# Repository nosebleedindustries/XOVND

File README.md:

# XOVND · web

Source for **xound.com** — `https://xovnd.com`.

## Stack

- **Next.js 14** (App Router, JSX — TypeScript migration deferred)
- **React 18**
- Static CSS in `app/globals.css` (merged from the original
  shared / auth / walkthrough stylesheets + per-page inline `<style>`
  blocks; Tailwind migration deferred)
- Vercel hosting, auto-deploy on push to `main`
- All sales currently route to **Moonbase hosted checkout** at
  `https://xound.moonbase.sh/buy/clvster`

## Status

**Phase 2B.1 — Next.js migration in progress.**

The Babel-in-browser multi-page static site has been ported to a
Next.js 14 App Router project. Two critical pages (landing `/` and
CLVSTER product `/clvster`) are fully ported. The remaining pages
(`/account`, `/subscription`, `/trials`, `/support`, `/forum`,
`/admin`, `/auth`, `/walkthrough`) are placeholder stubs that share
the header/footer chrome and link back to the legacy reference.

Original JSX files preserved under [`legacy/`](./legacy/) for
incremental porting.

## Routes

| Route | File | Status |
|---|---|---|
| `/` | `app/page.jsx` | ✅ ported |
| `/clvster` | `app/clvster/page.jsx` | ✅ ported (BUY → Moonbase) |
| `/trials` | `app/trials/page.jsx` | ✅ ported |
| `/account` | `app/account/page.jsx` | 🚧 placeholder |
| `/subscription` | `app/subscription/page.jsx` | 🚧 placeholder |
| `/support` | `app/support/page.jsx` | 🚧 placeholder |
| `/forum` | `app/forum/page.jsx` | 🚧 placeholder |
| `/admin` | `app/admin/page.jsx` | 🚧 placeholder |
| `/auth` | `app/auth/page.jsx` | 🚧 placeholder |
| `/walkthrough` | `app/walkthrough/page.jsx` | 🚧 placeholder |

## Local dev

```bash
npm install
npm run dev          # http://localhost:3000
```

`npm run build` for production build; `npm start` to serve it locally.

## Deploy

Vercel auto-detects Next.js, no config needed. Push to `main` →
auto-deploy to production. Push to any other branch → preview deploy
URL appears in PR / commit.

## Roadmap

Phase 2B detailed checklist in
[`docs/roadmap/Phase2B-Backend.md`](./docs/roadmap/Phase2B-Backend.md):
Supabase auth + DB, Moonbase webhook handler, support tickets, forum
threads, admin analytics, promotion management, email infrastructure,
SEO, mailing list, analytics.

## Shared infrastructure

- **Domain**: Cloudflare Registrar (`xovnd.com`)
- **DNS**: Cloudflare (with Vercel CNAMEs as `DNS only` — don't proxy)
- **Email**: Cloudflare Email Routing — `joan@xovnd.com` → Gmail
- **Hosting**: Vercel (free hobby tier)
- **Future**: Supabase (Postgres + Auth), Resend (email), Plausible
  (analytics), Sentry (errors), EmailOctopus (mailing list)

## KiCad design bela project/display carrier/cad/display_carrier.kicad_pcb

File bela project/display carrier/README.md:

# Display carrier — 2× LILYGO T-Display-S3 Long

A carrier PCB that mounts **two T-Display-S3 Long** AMOLED bars (ESP32-S3, 640×180)
**landscape and butted** as one wide ~1280×180 UI strip, and **sandwiches onto the
Beagle+Bela** via the PocketBeagle-2 header block (`U1`).

**This is the TOP board of the stack**, so **all connectors sit on the BACK (`B.Cu`)** —
`U1` (PB2 sandwich header), `JA`, `JB` and `J_PWR` face **down** into the Beagle+Bela
sandwich, while the two displays stay on the **front (`F.Cu`), facing up**. See
`renders/ensemble_stack_side.png` / `ensemble_stack_front.png` for the assembled stack.

**`U1` is at the carrier's RIGHT edge** (KiCad x≈165, below DS2): the Beagle+Bela sandwich
sits at that edge so the **Bela's audio jacks clear the carrier and reach a free panel edge**
(they'd be buried mid-board with U1 centred). Trade-off: the two displays sit to the left of
the sandwich (asymmetric). `JB` moved to x≈110 to clear the shifted U1.

**`U1` = MALE 2×18 pin headers** (`PinHeader_2x18_P2.54mm_Vertical` ×2), pins pointing
**down** so the carrier plugs into female sockets on top of the sandwich — you can't
mate two female sockets. `JA`/`JB` are **FEMALE 2×15 P1.27 mm sockets on the FRONT (`F.Cu`, display side)**
that **mirror the LILYGO module's own `P5` 30-pin breakout** — each display plugs straight down into its
socket for **power + data** (`+5V` on P5 pin 27 · `GND` · `TX` · `RX`), no cable. Each socket's pad-centre is
placed **coincident with the module's factory `P5` connector**, verified in the exported STEP (socket centre =
`P5` body centre to ±0.1 mm): DS1 `P5` at (69.9, 31.3), DS2 `P5` at (128.9, 18.7) — so the male `P5` inserts
into the socket receptacle and the panel seats at its true height. (The two sockets sit at opposite ends of
their panels because the modules are mirror-mounted — `P5` is off-centre on the module.)
The `ensemble_*` renders show the full stack aligned + sandwiched: `U1` sits over the
Beagle's P1/P2 headers and its pins insert into the sandwich; the MIDI board is the
ribbon satellite in front.

- The panels are **smart satellites** — each ESP32 renders its own graphics, so the
  carrier only carries **power + a PRU-serial link** to each (Bela Gem leaves no HW
  UART/SPI free — see `../docs/display-architecture.md`). PRU0→panel A, PRU1→panel B.
- `JA` / `JB` (2×15 P1.27 mm, = LILYGO `P5`): the panel plugs straight in — `+5V`(P5 pin 27) `· GND · TX · RX`.
- Displays are **mounted mirror-symmetric** (USB-C/electronics outward, screens meeting
  in the middle) for a continuous face. Module = **27.2 × 88.8 × 11.1 mm** (factory STEP).

Board ≈ **194 × 81 mm**, 2-layer, AISLER rules, with a 7 mm mounting border carrying
**4× M2.5 corner holes** (`H1–H4`). The wide board is carried on **4 brass M2.5 hex
standoffs (~23 mm)** from the enclosure floor to the corners — the central U1 header does
the wiring, the corner legs do the holding. `scripts/add_mounts.py` grows the border +
holes on the routed board (routing untouched; the new margin is a bare mounting border).

## Assembled stack height (male pins fully seated)
Measured from the factory 3D models with the carrier's 2×18 male header pushed **fully** into
the sandwich's female connector: **total PCB-stack height ≈ 36.2 mm** (device base → display glass).
- PocketBeagle 2 (PCB + headers): 0 → 8.7 mm
- Bela Gem (mated cape, PCB 11.7–13.3): **audio jacks up to 21.8 mm ← the limiting component**
- Carrier PCB: 22.8 → 24.4 mm (1 mm above the Bela jacks; male pins ~6 mm into the female)
- T-Display module → glass top: **36.19 mm**

**The height floor is the Bela's LINE IN/OUT jacks (21.8 mm)** — the carrier can't sit lower
without hitting them, so the male pins can only insert as far as that clearance allows. Lower-profile
or relocated jacks would let the stack compress further. Add the 1 mm aluminium enclosure +
top/bottom clearances (~3–5 mm) for the external height (~40–41 mm).

## Notes / to refine
- The `TDisplayS3Long` footprint's **mounting-hole positions are estimates** + the active-
  area seam offset should be verified against the factory DWG (`dimensions/` in the LILYGO
  repo) or a physical unit — then nudge the two modules for a perfect join.
- 3D model = the factory **`H685-PCB-3D.stp`** (from `T-Display-S3-Long-PCB-3D.zip`, LILYGO
  GitHub `dimensions/`) — not committed (7.75 MB); the footprint references it by path.

## Routing (done)
**Fully routed + fab-ready.** Freerouting 2.2.4, 2-layer (both signal). A parallel **clearance
sweep** {0.15, 0.175, 0.20, 0.25 mm} picked **0.25 mm** as the loosest that still routes clean
(most fab margin), then **GND poured on F.Cu + B.Cu** (solid pad connection), netclass clearance
**0.15 mm** (AISLER). Result: **0 unconnected, 68 tracks, 1 via, 0 hard DRC** (only 2 cosmetic
silk warnings — DS ref field near the edge + DS1/DS2 silk-rect overlap). Authoritative check =
`kicad-cli pcb drc` (verified: 0 shorting, 0 clearance, GND filled both layers, connectors on B.Cu).
Scripts: `scripts/carrier_export_dsn.py` (DSN, strips fp graphics by text so KiCad's exporter
doesn't choke on the big display outlines) + `scripts/carrier_route_variant.py <µm>` (one full
clearance variant → JSON). Routed back-side view: `renders/carrier_routed_bottom.png`.

## Power (rev: dedicated input)
The two AMOLEDs are hungry (~0.4–1 A peak), so they are **NOT** powered from the Beagle rail.
- **`J_PWR`** (2-pin screw terminal) = **+5V / GND** straight from the main PSU → feeds `JA`/`JB` → the panels.
- The **PB2 sandwich header (`U1`) carries only GND (common reference) + the data lines** (TX/RX/RST per panel).
- So display current never flows through the Beagle→Gem→carrier stack — the audio rail stays clean.

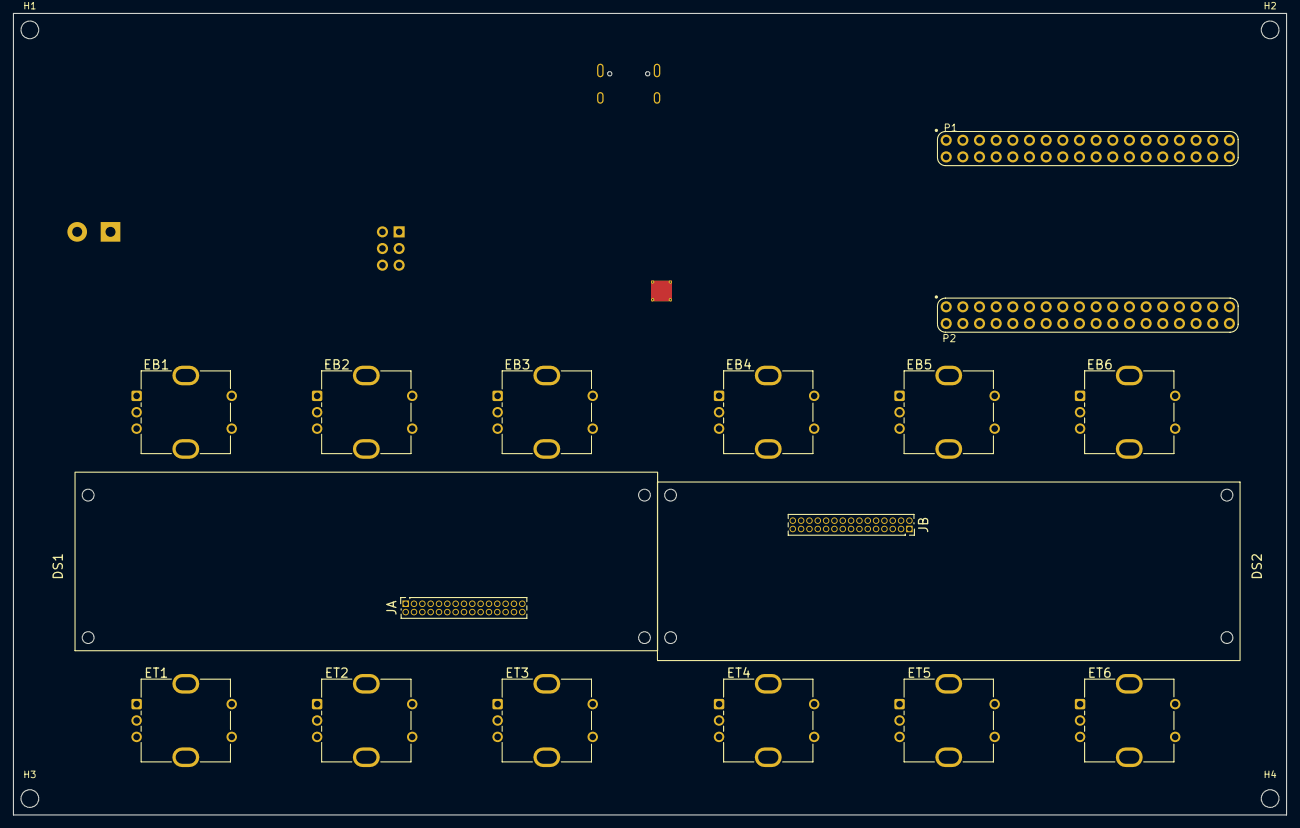
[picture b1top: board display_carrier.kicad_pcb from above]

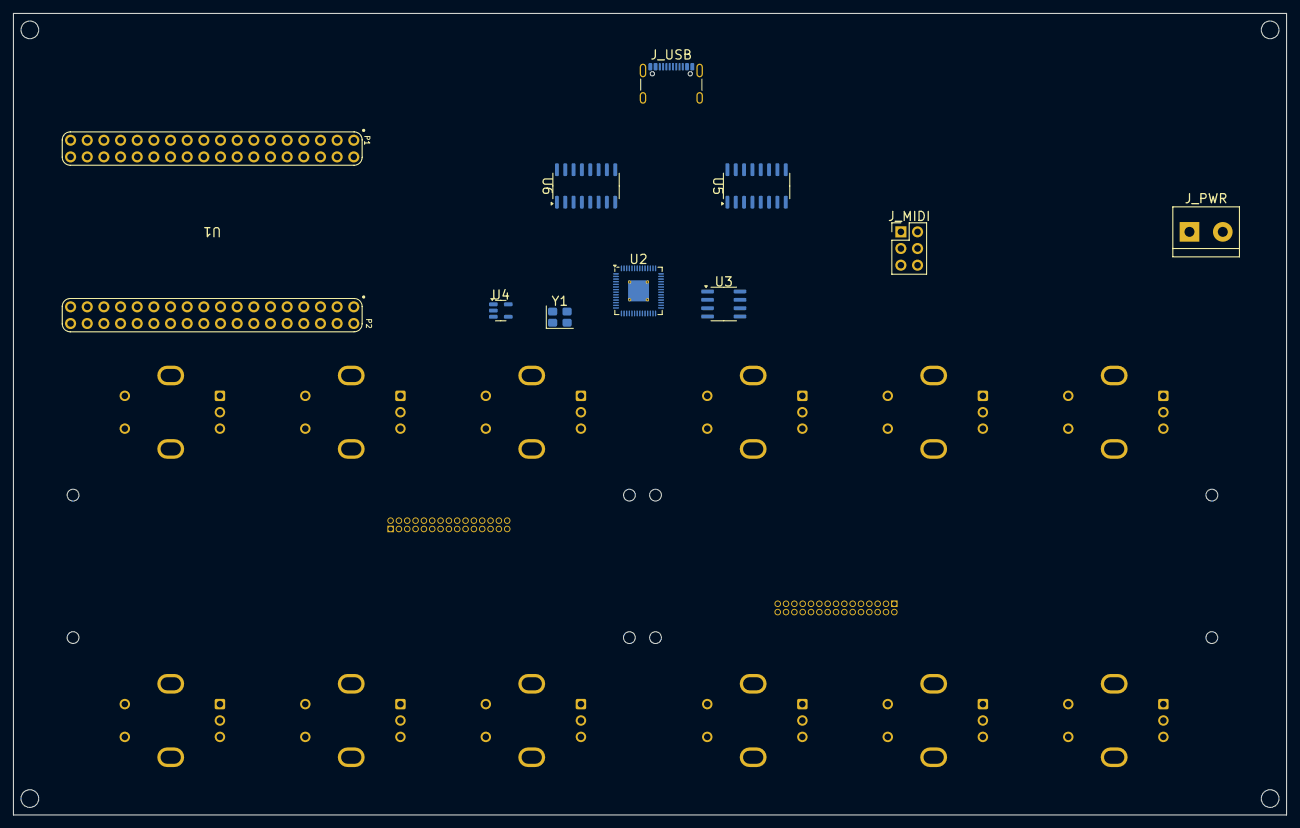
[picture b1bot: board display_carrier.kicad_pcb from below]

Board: 2 copper layers, 194.1 x 122.2 mm, 30 parts (10 on the bottom side), 9 nets, no tracks yet.

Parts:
DS1, DS2: T-Display-S3-Long; TDisplayS3Long
EB1, EB2, EB3, EB4, EB5, EB6: ENC; RotaryEncoder_PEC12R_Vertical
ET1, ET2, ET3, ET4, ET5, ET6: ENC; RotaryEncoder_PEC12R_Vertical
H1, H2, H3, H4: MountingHole_2.7mm_M2.5
JA: DISP_A; PinSocket_2x15_P1.27mm_Vertical
JB: DISP_B; PinSocket_2x15_P1.27mm_Vertical
J_MIDI: MIDI_HUB; PinHeader_2x03_P2.54mm_Vertical
J_PWR: PWR_IN; TerminalBlock_bornier-2_P5.08mm
J_USB: USB; USBC
U1: PocketBeagle2; PB2
U2: RP2040; RP2040_QFN56
U3: W25Q128; Flash_SOIC8
U4: 3V3; LDO_SOT235
U5, U6: 74HC165; SR_74HC165_SOIC16
Y1: 12MHz; XTAL_3225

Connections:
+3V3: J_MIDI.1, U1.P2.23 (3.3V)
+5V: JA.27, JB.27, J_PWR.1
DA_RX: JA.16, U1.P1.31 (PRU0.4)
DA_TX: JA.18, U1.P1.29 (PRU0.7)
DB_RX: JB.16, U1.P2.30 (PRU1.12)
DB_TX: JB.18, U1.P2.28 (PRU1.15)
GND: JA.1, JA.2, JB.1, JB.2, J_MIDI.2, J_MIDI.5, J_PWR.2, U1.P1.16 (GND), U1.P2.15 (GND)
MIDI_RX: J_MIDI.3, U1.P2.32 (PRU1.11)
MIDI_TX: J_MIDI.4, U1.P2.34 (PRU1.14)

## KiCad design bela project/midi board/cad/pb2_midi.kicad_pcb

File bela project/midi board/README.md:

# PocketBeagle 2 — MIDI board (TRS MIDI IN/OUT)

A small script-generated carrier PCB that adds **MIDI IN + MIDI OUT** (3.5 mm TRS
Type-A) to a **PocketBeagle 2**, designed to sit alongside the
[Bela Gem](https://bela.io/products/bela-gem-stereo-and-multi/) audio sandwich and
connect by a **6-way ribbon cable** — so the whole device stays thin.

Companion to the [Bela Gem CAD model](../README.md).

## What it is
- **MIDI IN** — opto-isolated (H11L1M) TRS-A input.
- **MIDI OUT** — resistor-driven TRS-A output.
- **Ribbon-connected** to the Beagle via `J3` (2×3 right-angle header), taps 4 pins of
  header **P2**: `+3V3 = P2.23`, `GND = P2.15`, `UART_RX = P2.5`, `UART_TX = P2.7`
  (**UART4** — chosen to avoid the Linux console UART0 and the Bela audio pins).
- **Jacks matched to the Bela audio jacks**: same **Lumberg 1503-03** part, same
  **10.7 mm** spacing, and mounted on **4× M2.5 hex standoffs** so the MIDI jacks land at
  the same panel plane and height (Z ≈ 16.2 mm) as the audio jacks — everything aligns on
  one enclosure face behind a **1 mm folded/laser-cut cover**.
- **Power on/off button** (`SW1`, Alps SKRTLAE010 side-actuated SMD): sits **in the same
  panel row, 10.7 mm** from the last jack, actuator co-planar with the jack fronts (X = 60.6).
  Soft-power to the Beagle via `J4` (`PWR_BTN`/`GND`/`+3V3`), conditioned on-board with
  `R5` (10 k pull-up, active-low) + `C3` (100 n debounce).
  - ⚠ **Set SW1's rotation so the actuator faces the panel edge** (verify vs the SKRTLAE010
    datasheet — no 3D model ships in KiCad, it's modelled by hand in the assembly). The
    actuator is a couple mm lower than the jack axis on a bare board; a tall side-switch or a
    ~1.7 mm riser puts it exactly on the jack centreline if you want the holes perfectly level.

Board: **44 × 40 mm**, single-sided population, 2-layer (AISLER rules).

## Files
```
cad/
  pb2_midi.kicad_pcb                 the board (KiCad 9)
  pb2_midi.step                      board 3D (STEP)
  pb2_midi_aligned_assembly.step     full aligned device: Bela sandwich + this board on
                                     hex spacers + ribbon + shared 1mm panel with 4 holes
scripts/
  gen_pcb.py                         script that builds the .kicad_pcb (parts + nets + DRC)
  merge_aligned.py                   builds the aligned assembly STEP (jack matching + spacers)
  merge_hat.py                       earlier viz (Gem hat + slim board + ribbon)
lib.pretty/                          footprints used (PB2, Lumberg jack, opto, header, holes)
renders/                             board render + connection-header diagram
bom.csv
```

## MIDI wiring
TRS **Type-A**: Tip = DIN-5, Ring = DIN-4, Sleeve = DIN-2.
- **IN:** J1.R → R1(220) → opto LED anode; opto LED cathode ← J1.T; D1 across the LED.
  Opto output: R4(470) pull-up to +3V3, collector → `UART_RX`.
- **OUT:** `UART_TX` → R2(220) → J2.T (tip); +3V3 → R3(220) → J2.R (ring); J2.S → GND.

## ⚠ Electrical note — Gem + MIDI
`UART4` (P2.5/P2.7) is free **only when the Bela Gem is NOT fitted** (the Gem uses those
pins for audio). For a **standalone MIDI** PocketBeagle this ribbon board is correct. If
you want **Gem audio *and* MIDI on one Beagle**, run MIDI over **USB** instead — no free
serial UART is available with the Gem on.

## Rebuild
```
"C:/Program Files/KiCad/9.0/bin/python.exe" scripts/gen_pcb.py      # -> pb2_midi.kicad_pcb + DRC
kicad-cli pcb export step --subst-models --no-dnp -o cad/pb2_midi.step cad/pb2_midi.kicad_pcb
FreeCADCmd scripts/merge_aligned.py                                 # -> aligned assembly STEP
```

## Routing
Routed with **Freerouting 2.2.4** (2-layer, both F/B signal) then **GND poured on F.Cu + B.Cu**
(solid pad connection). AISLER 2-layer rules: track 0.25, space 0.15, via 0.7/0.3, edge 0.3.
- `scripts/route_export_dsn.py` → `routing/pb2_midi.dsn` (clearance 0.15) → Freerouting `-mp 40`
  → `routing/pb2_midi.ses` → `scripts/route_import_ses.py` (import + GND pour).
- **Result: routing_complete = True, 0 unconnected, 2 vias, GND plane both layers.**

```
kicad python  gen_pcb.py            # clean board
kicad python  route_export_dsn.py   # -> routing/pb2_midi.dsn
java -jar freerouting-2.2.4.jar -de routing/pb2_midi.dsn -do routing/pb2_midi.ses -mp 40
kicad python  route_import_ses.py   # import SES + pour GND -> pb2_midi.kicad_pcb
```

## Blender renders (process documentation)
Photoreal Cycles renders of the current build state live in `renders/blender_*.png`
(hero / detail / top). Pipeline via the **blender-mcp** socket:
- Boards exported from KiCad as **GLB with copper traces** (`kicad-cli pcb export glb
  --include-tracks --include-zones --include-silkscreen --include-soldermask`) — the MIDI
  board and the factory Bela Gem both show real traces + silk + soldermask.
- PocketBeagle 2 = STEP → OBJ. Case panel, hex spacers, ribbon, TRS jacks and the power
  button are built as Blender primitives (`blender/bl_build2.py`); 3-point + warm orange
  rim lighting, AgX view transform.
- `blender/bl.py` drives Blender over the addon socket (127.0.0.1:9876); `bl_import.py`
  imports + normalizes, `bl_build2.py` assembles + materials + Cycles, `bl_hero.py` renders.

## Status
- **Routed + GND-poured, fab-ready for AISLER.** Jacks + power button aligned to the Bela audio
  jacks (spacing/plane/height), hex-spacer mounts, DRC **0 errors / 0 unconnected**.
- Conservative KiCad courtyards were shrunk (jacks fit 10.7 mm as on the Bela) and footprint
  silkscreen graphics dropped. One residual **silk-over-copper warning** (C1 ref over its pad) —
  cosmetic; AISLER auto-clips silk off pads.

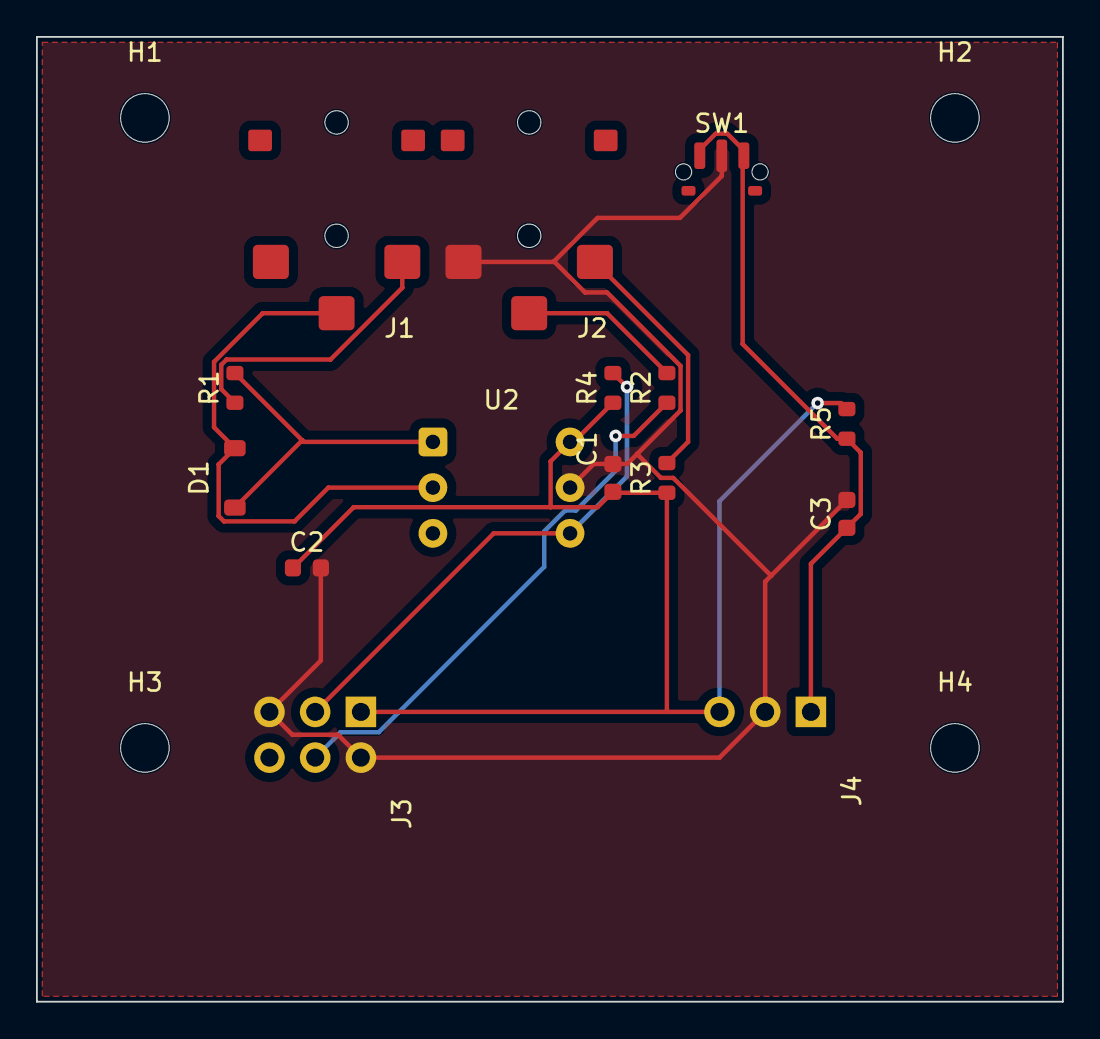
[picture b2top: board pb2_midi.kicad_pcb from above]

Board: 2 copper layers, 57.0 x 53.6 mm, 19 parts (0 on the bottom side), 10 nets.

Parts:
C1, C2, C3: 100n; C_0603_1608Metric
D1: 1N4148; D_SOD-123
H1, H2, H3, H4: M2.5; MountingHole_2.7mm_M2.5
J1: MIDI_IN; Jack_3.5mm_Lumberg_1503_03_Horizontal
J2: MIDI_OUT; Jack_3.5mm_Lumberg_1503_03_Horizontal
J3: RIBBON; PinHeader_2x03_P2.54mm_Horizontal
J4: PWR_HDR; PinHeader_1x03_P2.54mm_Horizontal
R1, R2, R3: 220; R_0603_1608Metric
R4: 470; R_0603_1608Metric
R5: 10k; R_0603_1608Metric
SW1: PWR; SW_Push_1P1T-MP_NO_Horizontal_Alps_SKRTLAE010
U2: H11L1M; DIP-6_W7.62mm

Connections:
+3V3: C1.1, C2.1, J3.1, J4.3, R3.1, R4.1, R5.2, U2.6
GND: C1.2, C2.2, C3.2, J2.S, J3.2, J3.5, J4.2, SW1.2, U2.5
MIDI_IN_A: D1.1, R1.2, U2.1
MIDI_IN_K: D1.2, J1.T, U2.2
MIDI_IN_RING: J1.R, R1.1
MIDI_OUT_RING: J2.R, R3.2
MIDI_OUT_TIP: J2.T, R2.2
PWR_BTN: C3.1, J4.1, R5.1, SW1.1
UART_RX: J3.3, R4.2, U2.4
UART_TX: J3.4, R2.1

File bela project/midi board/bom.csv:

Refs,Qty,Value,Footprint,MPN,Description
J1 J2,2,3.5mm TRS,Jack_3.5mm_Lumberg_1503_03_Horizontal,Lumberg 1503 03,MIDI IN / MIDI OUT — 3.5mm TRS Type-A jack (same part + 10.7mm spacing as the Bela audio jacks so they align on the panel)
SW1,1,PWR,SW_Push_1P1T-MP_NO_Horizontal_Alps_SKRTLAE010,Alps SKRTLAE010,Power on/off — side-actuated SMD momentary push button; soft-power to the Beagle. Placed in the panel row 10.7mm from J2 (actuator co-planar with the jack fronts). NOTE: set SW1 rotation so the actuator faces the panel edge (verify vs datasheet).
U2,1,H11L1M,DIP-6_W7.62mm,H11L1M,High-speed optocoupler — MIDI IN opto-isolation (1=Anode 2=Cathode 3=NC 4=Vo 5=GND 6=Vcc)
D1,1,1N4148,D_SOD-123,1N4148W-7-F,Reverse-protection diode across the opto input LED
R1,1,220,R_0603_1608Metric,RC0603FR-07220RL,MIDI IN current-limit resistor
R4,1,470,R_0603_1608Metric,RC0603FR-07470RL,Opto output pull-up to +3V3
R2 R3,2,220,R_0603_1608Metric,RC0603FR-07220RL,MIDI OUT tip/ring series resistors (TRS Type-A)
R5,1,10k,R_0603_1608Metric,RC0603FR-0710KL,Power-button pull-up to +3V3 (active-low)
C1 C2 C3,3,100n,C_0603_1608Metric,CL10B104KB8NNNC,+3V3 decoupling (C1/C2) + power-button debounce (C3)
J3,1,2x3 R/A,PinHeader_2x03_P2.54mm_Horizontal,2x3 2.54mm right-angle header,Ribbon header to PocketBeagle 2 — 1=+3V3 2=GND 3=UART_RX 4=UART_TX 5=GND 6=NC
J4,1,1x3 R/A,PinHeader_1x03_P2.54mm_Horizontal,1x3 2.54mm right-angle header,Power-button header to the sandwich — 1=PWR_BTN 2=GND 3=+3V3
H1 H2 H3 H4,4,M2.5,MountingHole_2.7mm_M2.5,-,Mounting holes for the hex standoffs that lift the board to audio-jack height
-,4,hex standoff,M2.5 ~11.6mm,-,"HARDWARE: M2.5 hex spacers — lift the MIDI board so its jacks + button sit at the Bela audio-jack height (Z≈16.2mm). Use 11mm+washer or 12mm."
-,1,ribbon,6-way IDC 2x3,-,"HARDWARE: 6-conductor flat cable, J3 <-> PocketBeagle 2 header P2 (taps P2.23/15/5/7)"
-,1,cable,3-way,-,"HARDWARE: 3-wire from J4 to the sandwich (PWR_BTN to a Beagle GPIO / power-button input, + GND + 3V3)"
-,2,IDC socket,2x3 2.54mm,-,HARDWARE: IDC ribbon terminations (one on J3, one on the P2 tap)

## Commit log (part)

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2026-05-21 Fix SSR crash: guard localStorage helpers with typeof window
    useState initializers run on the server during SSR, so calling
    localStorage.getItem() at render time crashes the build. Guard the
    read/write helpers (readObj, readJSON, readThreads/writeThreads) and
    the forum category useState initializer with typeof window checks so
    they return safe defaults on the server.
    This is what was breaking every Vercel deploy since e819004.
2026-05-21 Swap header/footer logo to final XOVND wireframe wordmark
    Replace dirty-yellow PNG with the clean wireframe-letter JPG. New
    asset is wider (16:9-ish), already the right pale yellow, so the
    heavy hue-rotate/saturation/double-shadow bloom comes off and a
    single subtle drop-shadow remains. Header height 56→44, footer 40→32
    to suit the wider aspect.
2026-05-21 Fix Vercel build: import Fragment, drop stale port leftovers
    Three ESLint/runtime errors were failing every Next.js production build:
    - app/account/page.jsx: <Fragment> used but not imported (jsx-no-undef);
    also four useAccEffect aliases left over from the mechanical port
    → renamed to useEffect.
    - app/clvster/page.jsx: <Fragment> used but not imported.
    - app/clvster/page.jsx: useAuth called conditionally
2026-05-21 Logo: bigger + mix-blend-mode: screen to drop JPG black border
    User reported a visible rectangle around the wordmark (JPG compression
    keeps the background just shy of pure #000). screen blend makes dark
    pixels transparent against the black header so only the yellow
    wireframe shows. Header 110→140, footer 44→52.
2026-05-21 Logo: drop yellow halo, add pillow-rounded mask
    Removed every drop-shadow/filter on the wordmark (base + hover) so the
    yellow glow is gone. Added border-radius (32px header, 14px footer) to
    clip any residual JPEG-compression noise at the corners into a soft
    pillow contour. Combined with mix-blend-mode: screen this should give
    a clean letters-only render against the black header.
2026-05-21 Logo: top edge at viewport y=0 + click toggles Perlin dot-grid marquee
    - Header logo margin-top -28→-46 so the pillow's top edge is flush
    with the very top of the page (extends through the announce strip).
    - Clicking the logo on any page toggles the marquee between scrolling
    text and an animated Perlin dot-grid. Vanilla canvas port of the
    user's p5 sketch — black dots on yellow, dot diameter modulated by
    smooth 2D value noise, offset incremented each frame so the field
2026-05-21 Logo: shrink so its box no longer occludes the hero title
    Reduced .brand-glow-ring height 140→96 and margin-bottom -88→-44 so
    the pillow sits within the announce strip + nav row instead of
    extending into the hero section. User reported clicks on the
    "CLVSTER / Algorithmic Sequencer" title were being blocked by the
    oversized logo wrapper. Border-radius nudged 32→24 to keep the
    pillow proportion at the new size.
2026-05-21 Logo: springy bounce on click (squash + overshoot)
    Adds a transient .springing class to the glow-ring wrapper on click
    that triggers a cubic-bezier(.34,1.56,.64,1) keyframe — quick squash
    to 0.86, overshoot to 1.10 with a tiny rotation kick, settle to 1.
    Class is removed after 600ms so the animation can re-fire on the
    next click. Pairs with the existing marquee pattern toggle.
2026-05-21 Logo: bigger pillow + thinner subtler rotating glow
    Pillow 96→124px tall, radius 24→30, margin-bottom -44→-60 so the
    visible bottom still stays within the nav and doesn't occlude the
    hero title. Rim padding 3→1.5 (half thickness), alphas dropped from
    0.9→0.55 and white 1.0→0.7. Outer halo opacity 0.7→0.35, blur
    12→8, inset shrunk so the bloom is felt rather than seen. Orbit
    slowed 3.4→4.6s to match the lower energy.
2026-05-21 Cleanup: drop Praise + Awards + Product grid from landing; footer to brand+legal only; video auto-unmute on first interaction
    Page deletions (just removed from the render tree; component code
    stays in the file so we can revive easily):
    - <Testimonials />: fake quotes about nonexistent plugins (PRISMA,
    MONOLITH, DRIFT) — confusing for visitors.
    - <Awards />: placeholder "Plugin of the Year" badges from invented
    magazines.
2026-05-21 Wire landing-page Cart checkout button to Moonbase
    The Cart component in app/page.jsx had no onClick on its Checkout
    button at all — the user reported it didn't land anywhere. Added
    the same MOONBASE_CHECKOUT handler used by the shared CartDrawer.
    Note: the target URL still 404s because the CLVSTER product has
    not yet been created on the Moonbase storefront — that's a
    backend/admin task, not code. Wiring is in place for when it lands.
2026-05-21 Product page carousel: lead slide is the promo video, not a screenshot
    Replaced /assets/clvster-ui.png with the existing
    /assets/clvster-promo.mp4 (the same 8 MB 720p clip already shipping
    on the landing page — no additional compression needed). User can
    still add screenshots via the Replace button to extend the
    carousel.
2026-05-21 Logo: gentle continuous bob; apex hits viewport y=0 every cycle
    Reset margin-top to -46 (exact alignment, no overshoot clip) and
    added a 1.9s ease-in-out translateY(0 -> 6 -> 0) loop so the pillow
    breathes/bounces lightly with its top edge re-touching the very top
    of the viewport each cycle. The click-springy keyframe still wins
    when .springing is added because CSS animation property is overwritten.
2026-05-21 Add Beta Section + modal + admin list; restore original commerce buttons
2026-05-21 Code-only access flow: AccessModal replaces stub login; admin shows redemption counts
2026-05-21 Hotfix: landing page crashed for code-redeemed users (user.email undefined)
2026-05-21 Swap clvster-promo.mp4 with new 2:12 build (sin-audio-1, audio kept)
2026-05-21 Swap product video to final promo cluster ya (overwrites previous swap)
2026-05-21 Supabase: leads + redemptions tables; /admin reads from server; AccessModal posts server-side
2026-05-21 Persistent TODO: tomorrow's priorities + this-week + later
2026-05-22 TOMORROW: mark Moonbase sales live (2026-05-22)
2026-05-24 Landing hero pillow: bigger (720→920px max, 86%→98% width) and shifted up 56px so it sits over the gen-art band
2026-05-25 trials: wire CLVSTER button to Moonbase buy page, disable KANTIAN
    Both buttons were placeholder alert() calls that just popped a
    "Download starting…" toast and never actually downloaded anything —
    the reason a beta tester opening /trials saw nothing happen.
    - CLVSTER demo button now navigates to the public Moonbase store
    page (https://xound.moonbase.sh/buy/clvster) where the demo is
    hosted alongside the buy flow. Opens in a new tab.
2026-05-25 trials: host CLVSTER installer directly, bypass Moonbase buy page
    Moonbase's /buy/clvster URL only exposes the purchase flow — there
    is no public "trial" or "demo" route exposed. Linking the trials
    page button there meant testers got dropped on a checkout screen
    instead of a download.
    Drop the 8.12 MB installer into XOVND's public/downloads/ so Vercel
    serves it as a static file at https://xovnd.com/downloads/CLVSTER-1.0.0-Win.exe.
2026-05-26 trials: refresh installer with Moonbase trial-latch fix (KantianOctoSeq b3879b3)
    Bundled VST3 + Standalone now carry the latch that defeats the
    Moonbase SDK's trial=1/trial=0 callback retraction race — the LICENSE
    pill correctly shows TRIAL · N DAYS LEFT for fresh trial activations
    instead of falsely reading ✓ LICENSED.
    Also includes the transition-only dedup version of clvsterLicLog so
    %APPDATA%\CLVSTER\license-debug.log is kept clean for end users while
2026-05-28 Hero: swap landing video + defer playback to first user activity
    - Replaced public/assets/clvster-promo.mp4 with the new "Video Project
    40" cut (49 MB, up from 8.8 MB — heavier asset, worth a TinyVideo /
    ffmpeg pass before PB launch but keeping full quality for now).
    - Dropped `autoPlay` from the <video> tag. The Hero useEffect now
    listens for mousemove + pointerdown + keydown + scroll + touchstart;
    whichever fires first kicks the video off and tries to unmute. If
2026-05-28 Hero: drop CLVSTER pillow logo + tagline, video is now the first element
    Removed the rotating-rim CLVSTER pillow-video logo + the "Cluster
    Chain Sequencer" tagline from the hero-right column. The promo video
    (played on first user activity per 53fc543) now sits directly under
    the HeroGenArt background — it's the visual lead for the hero. Ticker
    strip stays below the video as before.
2026-05-29 trials: revert installer to pre-engine-autoplay (playhead regression)
    Pairs with KantianOctoSeq 25b2752. The engine-side autoplay attempt
    killed every UI playhead on transport play; reverted until the cause
    is understood. JS-side cycling restored (works with GUI open).
2026-05-29 trials: refresh installer with cluster C/P chip mode-gating
2026-05-29 trials: refresh installer with stateful Nibbler
2026-05-29 trials: refresh installer with gate-to-step-duration fix
2026-05-29 trials: refresh installer with tour persist + snap_shot anchor
2026-05-29 trials: stable installer URL + host KANTIAN .amxd
    - CLVSTER installer now at /downloads/CLVSTER-Win.exe (no version in
    the filename). Old /downloads/CLVSTER-1.0.0-Win.exe removed; anyone
    with the old URL will get a 404 prompting them to revisit /trials
    for the current download.
    - KANTIAN .amxd hosted at /downloads/KANTIAN.amxd (478 KB). The
    trials page entry's "Coming soon" placeholder is now a real link;
2026-05-30 trials: refresh installer (Quickstart: button on camera + filled-yellow highlight + BOOLEANS pulse + harmony pillow chrome)
2026-05-30 trials: refresh installer (Snapshot panel auto-open + info popup pitch/rhythm icons + Ctrl+Alt+Q reset + script preset-loss guard)
2026-05-30 trials: refresh installer (Color-coding: pitch=pale pink, rhythm=pale mint across rails + harmony button)
2026-05-30 trials: refresh installer (Snapshot drawer widened 260 -> 320 px so internal controls breathe)
2026-05-30 trials: refresh installer (Boolean pair-op cards: opaque black bg + coloured letters + 1100 ms continuous flash matching BOOLEANS button)
2026-05-30 trials: refresh installer (Snapshot sequencer as native pop-out window + treble/stopwatch Unicode icons)
2026-05-30 trials: refresh installer (Camera moved below harmony button + ALGORITHMS description popup auto-shows on first open)
2026-05-31 trials: refresh installer (Snapshot pop-out fills+scales window proportionally; camera aligns under harmony when global rail expanded)
2026-05-31 trials: refresh installer (Snapshot pop-out: empty-slot click stores directly; hide in-panel drag-cross + dock-X (OS window handles move/close))
2026-05-31 trials: refresh installer (Pop-out: no splash; HARMONY button LOCK-sized + aligned to LOCK column + 3px up; camera on LOCK column; WORKFLOW pillow moved to central-panel bottom-right)
2026-05-31 trials: refresh installer (Camera popup flips past full width; harmony nudged right to align LOCK; LOCK/DICE/ERASER converted to pillow buttons with rotating rim)
2026-05-31 trials: refresh installer (Floating buttons pushed right (12px panel gap); camera back to bottom; live piano-roll: engine streams pattern to pop-out so dots update each cycle, freeze on snapshot)
2026-05-31 trials: refresh installer (Floating buttons unified pink + thin lines; harmony moved to gutter (aligned under LOCK, 72x72); remove pitch/rhythm icon glow)
2026-05-31 trials: refresh installer (Cache-buster: stamp compile-time build id onto page + script URLs so WebView2 never serves stale JS after install)
2026-05-31 trials: refresh installer (Gutter buttons further left (clear panel gap); camera into gutter column below harmony; dice+eraser now pink thin-stroke icons matching harmony)
2026-05-31 trials: refresh installer (Dice: restore the real 3D-rotation cube, recoloured to pink thin-line style)
2026-05-31 trials: refresh installer (Eraser: restore original slide-and-erase illustration in pink thin-line style; bigger lock icon)
